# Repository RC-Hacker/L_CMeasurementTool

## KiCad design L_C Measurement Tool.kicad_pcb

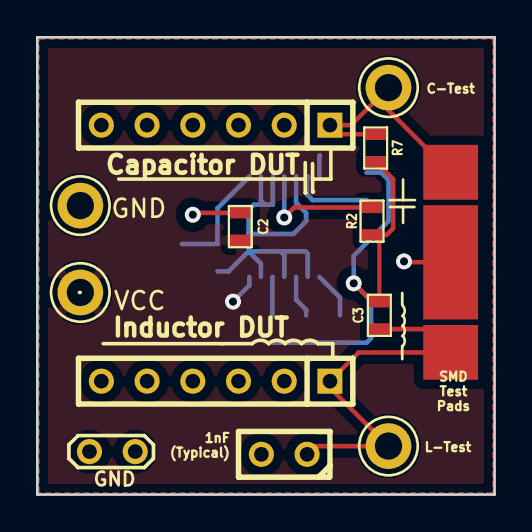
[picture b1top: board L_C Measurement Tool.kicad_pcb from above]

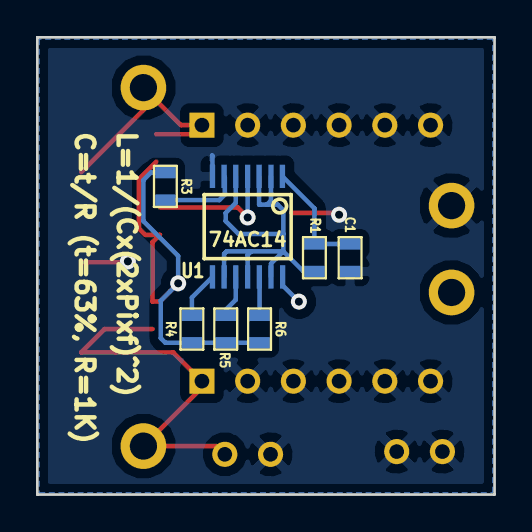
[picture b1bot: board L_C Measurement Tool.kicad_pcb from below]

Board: 2 copper layers, 25.4 x 25.4 mm, 20 parts (7 on the bottom side), 12 nets.

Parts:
C1: 47nF; SM0603
C2: 100nF; SM0603
C3: 10pF; SM0603
C4: 1nF; C1
P1: VCC; TESTPOINT_1PIN
P2: GND; TESTPOINT_1PIN
P3, P4: SIL6; SIL-6
P5: C-Test; TESTPOINT_1PIN
P6: L-Test; TESTPOINT_1PIN
P7: LC_SMD_TEST_PAD; LC_SMD_Test_Pad
P8: GND; TESTPOINT
R1: 6.8K; SM0603
R2, R3, R4, R5, R6: 220; SM0603
R7: 1K; SM0603
U1: 74AC14; TSSOP14

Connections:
GND: C1.2, C2.2, C4.2, P2.1, P3.2, P3.3, P3.4, P3.5, P3.6, P4.2, P4.3, P4.4, P4.5, P4.6, P7.2, P8.1, U1.7
unnamed: C3.2, C4.1, P4.1, P6.1, P7.3
unnamed: C1.1, R1.1, U1.1
unnamed: P3.1, P5.1, P7.1, R7.2
unnamed: R1.2, U1.2, U1.3, U1.5, U1.9, U1.11, U1.13
unnamed: R4.1, U1.8
unnamed: R2.1, U1.4
unnamed: R3.1, U1.6
unnamed: R5.1, U1.10
unnamed: C3.1, R2.2, R3.2, R4.2, R5.2, R6.2, R7.1
unnamed: R6.1, U1.12
VCC: C2.1, P1.1, U1.14
